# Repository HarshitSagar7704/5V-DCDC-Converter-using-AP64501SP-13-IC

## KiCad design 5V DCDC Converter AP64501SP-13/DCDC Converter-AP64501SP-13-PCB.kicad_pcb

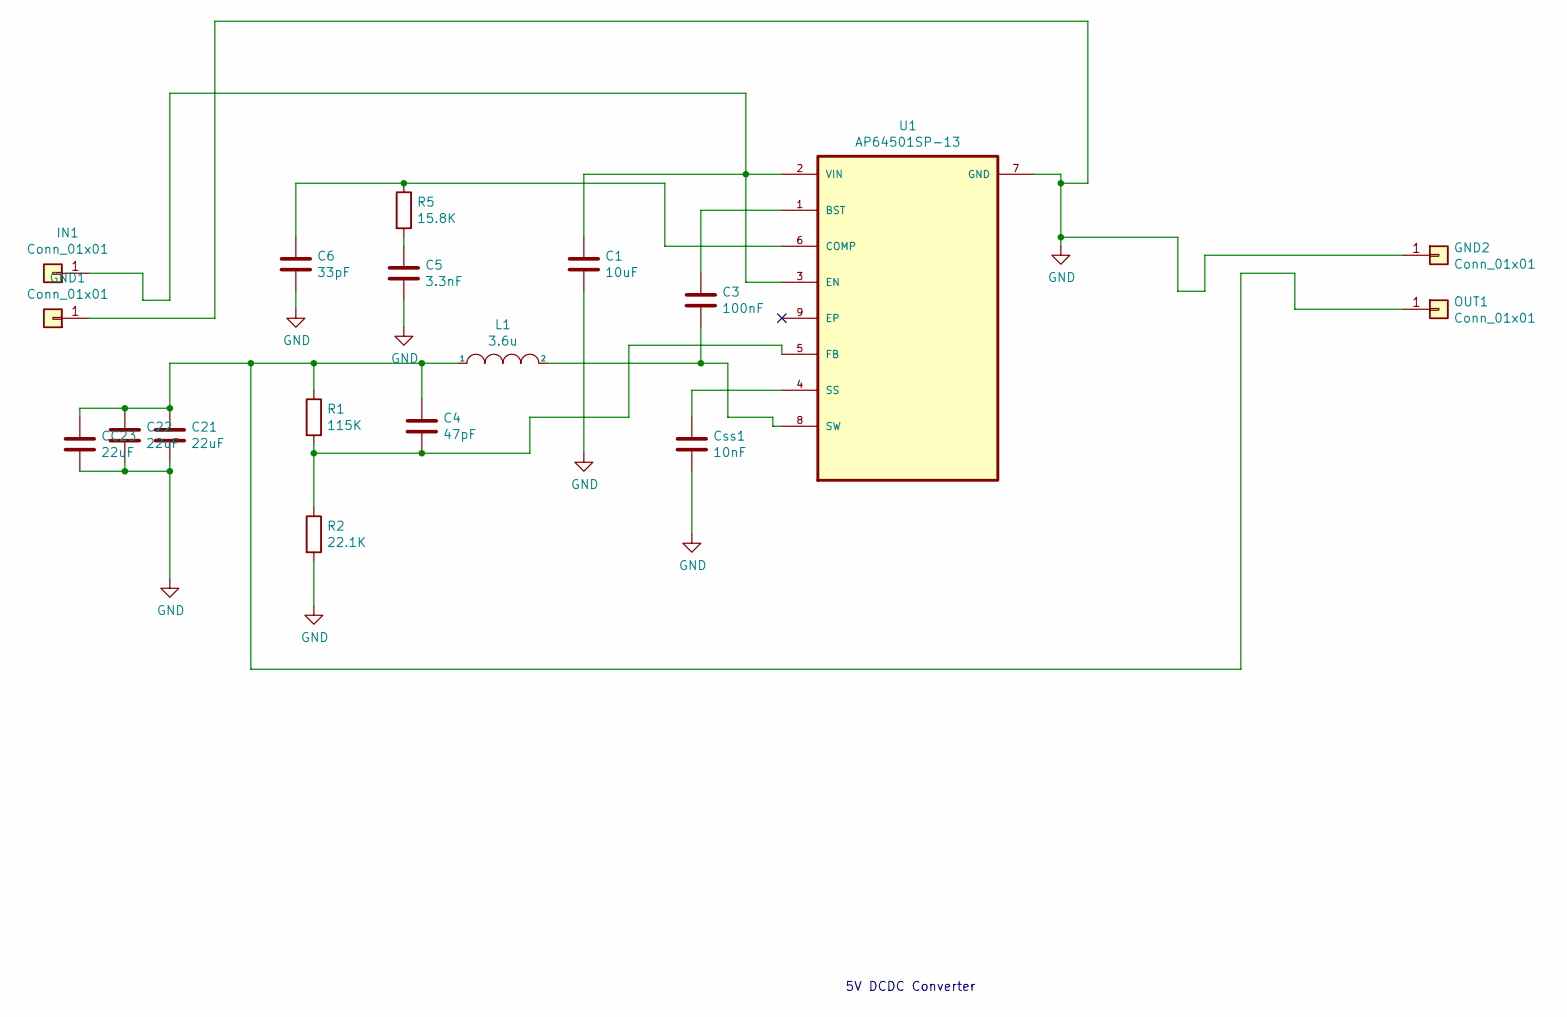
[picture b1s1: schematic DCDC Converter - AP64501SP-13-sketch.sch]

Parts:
C1: 10uF; C_1210_3225Metric
C3: 100nF; C_1210_3225Metric
C4: 47pF; C_0805_2012Metric
C5: 3.3nF; C_0603_1608Metric
C6: 33pF; C_0603_1608Metric
C21, C22: 22uF; C_2220_5650Metric
CC23: 22uF; C_2220_5650Metric
Css1: 10nF; R_0402_1005Metric
GND1, GND2: Conn_01x01; Pin_D1.0mm_L10.0mm
IN1: Conn_01x01; Pin_D1.0mm_L10.0mm
L1: 3.6u; L_10.4x10.4_H4.8
OUT1: Conn_01x01; Pin_D1.0mm_L10.0mm
R1: 115K; R_0201_0603Metric
R2: 22.1K; R_0201_0603Metric
R5: 15.8K; R_0201_0603Metric
U1: AP64501SP-13; SOIC127P600X163-9N

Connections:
GND: C1.2, C5.2, C6.2, C21.2, C22.2, CC23.2, Css1.2, GND1.1, GND2.1, R2.2, U1.7 (GND)
unnamed: C1.1, IN1.1, U1.2 (VIN), U1.3 (EN)
unnamed: C3.1, U1.1 (BST)
unnamed: C3.2, L1.2, U1.8 (SW)
unnamed: C4.2, R1.2, R2.1, U1.5 (FB)
unnamed: C5.1, R5.2
unnamed: C6.1, R5.1, U1.6 (COMP)
unnamed: C4.1, C21.1, C22.1, CC23.1, L1.1, OUT1.1, R1.1
unnamed: Css1.1, U1.4 (SS)

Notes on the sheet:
5V DCDC Converter

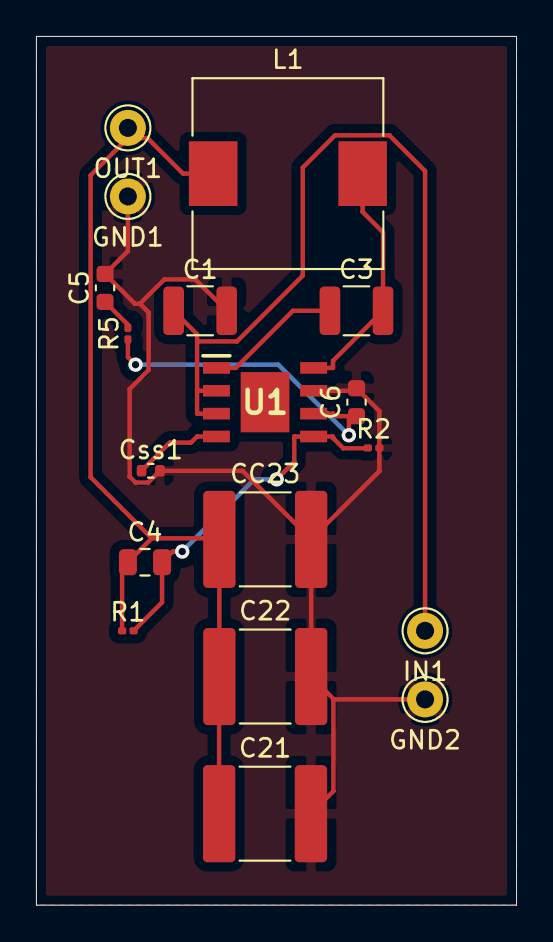
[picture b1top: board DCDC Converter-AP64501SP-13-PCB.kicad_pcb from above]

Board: 2 copper layers, 26.7 x 48.3 mm, 18 parts (0 on the bottom side), 9 nets.
